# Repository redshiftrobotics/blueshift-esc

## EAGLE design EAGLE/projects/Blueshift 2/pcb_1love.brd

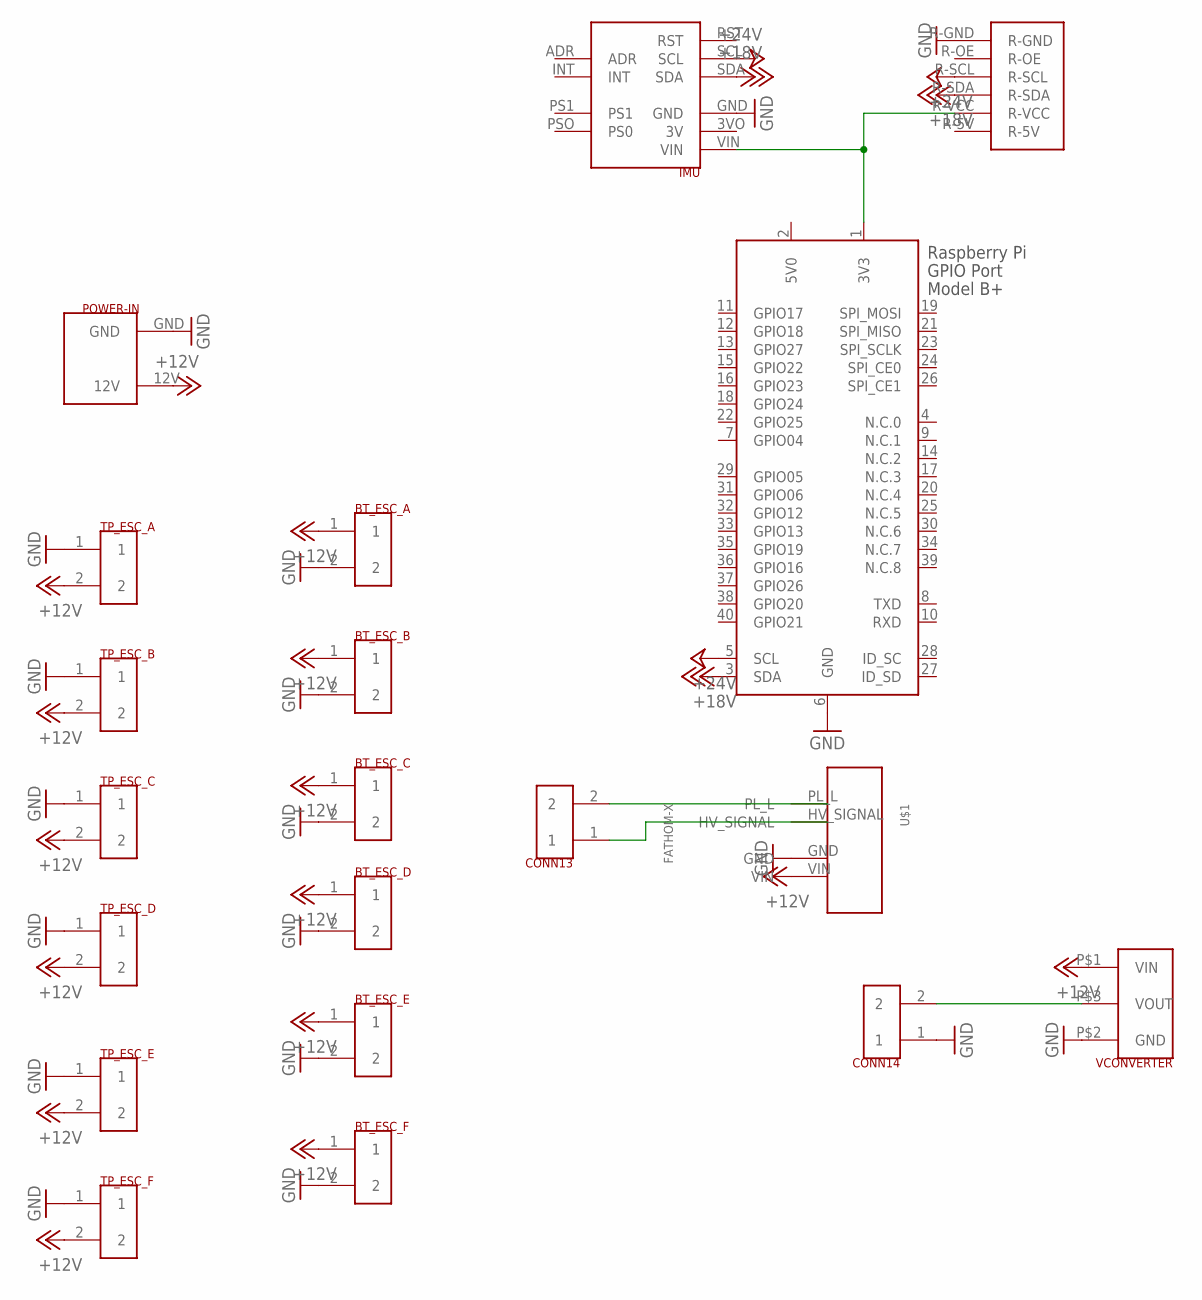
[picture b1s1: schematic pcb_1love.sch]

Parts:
BT_ESC_A: 2CONTACT_ULTRAFIT_R/A; 2CONTAC_ULTRAFIT_R/A
BT_ESC_B: 2CONTACT_ULTRAFIT_R/A; 2CONTAC_ULTRAFIT_R/A
BT_ESC_C: 2CONTACT_ULTRAFIT_R/A; 2CONTAC_ULTRAFIT_R/A
BT_ESC_D: 2CONTACT_ULTRAFIT_R/A; 2CONTAC_ULTRAFIT_R/A
BT_ESC_E: 2CONTACT_ULTRAFIT_R/A; 2CONTAC_ULTRAFIT_R/A
BT_ESC_F: 2CONTACT_ULTRAFIT_R/A; 2CONTAC_ULTRAFIT_R/A
CONN13, CONN14: 2CONTACT_ULTRAFIT_R/A; 2CONTAC_ULTRAFIT_R/A
IMU: IMU
POWER-IN: 2-CONTACT-SUPER
PWM_EXT: PWM_EXTENDER-SIMPLE
TP_ESC_A: 2CONTACT_ULTRAFIT_R/A; 2CONTAC_ULTRAFIT_R/A
TP_ESC_B: 2CONTACT_ULTRAFIT_R/A; 2CONTAC_ULTRAFIT_R/A
TP_ESC_C: 2CONTACT_ULTRAFIT_R/A; 2CONTAC_ULTRAFIT_R/A
TP_ESC_D: 2CONTACT_ULTRAFIT_R/A; 2CONTAC_ULTRAFIT_R/A
TP_ESC_E: 2CONTACT_ULTRAFIT_R/A; 2CONTAC_ULTRAFIT_R/A
TP_ESC_F: 2CONTACT_ULTRAFIT_R/A; 2CONTAC_ULTRAFIT_R/A
U$1: FATHOM-X
VCONVERTER: VOLTAGE_CONVERTER; VOLTAGE_CONVERTERS
X1: RASPI_BOARD_B+_F; RASPI_BOARD_B+_FULL

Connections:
5V0: X1.2 (5V0)
+12V: BT_ESC_A.1, BT_ESC_B.1, BT_ESC_C.1, BT_ESC_D.1, BT_ESC_E.1, BT_ESC_F.1, POWER-IN.12V, TP_ESC_A.2, TP_ESC_B.2, TP_ESC_C.2, TP_ESC_D.2, TP_ESC_E.2, TP_ESC_F.2, VCONVERTER.P$1 (VIN)
+18V: IMU.SDA, PWM_EXT.R-SDA, X1.3 (SDA)
+24V: IMU.SCL, PWM_EXT.R-SCL, X1.5 (SCL)
GND: BT_ESC_A.2, BT_ESC_B.2, BT_ESC_C.2, BT_ESC_D.2, BT_ESC_E.2, BT_ESC_F.2, CONN14.1, IMU.GND, POWER-IN.GND, PWM_EXT.R-GND, TP_ESC_A.1, TP_ESC_B.1, TP_ESC_C.1, TP_ESC_D.1, TP_ESC_E.1, TP_ESC_F.1, VCONVERTER.P$2 (GND), X1.6 (GND)
unnamed: CONN13.2, U$1.PL_L
unnamed: CONN13.1, U$1.HV_SIGNAL
unnamed: CONN14.2, VCONVERTER.P$3 (VOUT)
unnamed: IMU.VIN, PWM_EXT.R-VCC, X1.1 (3V3)

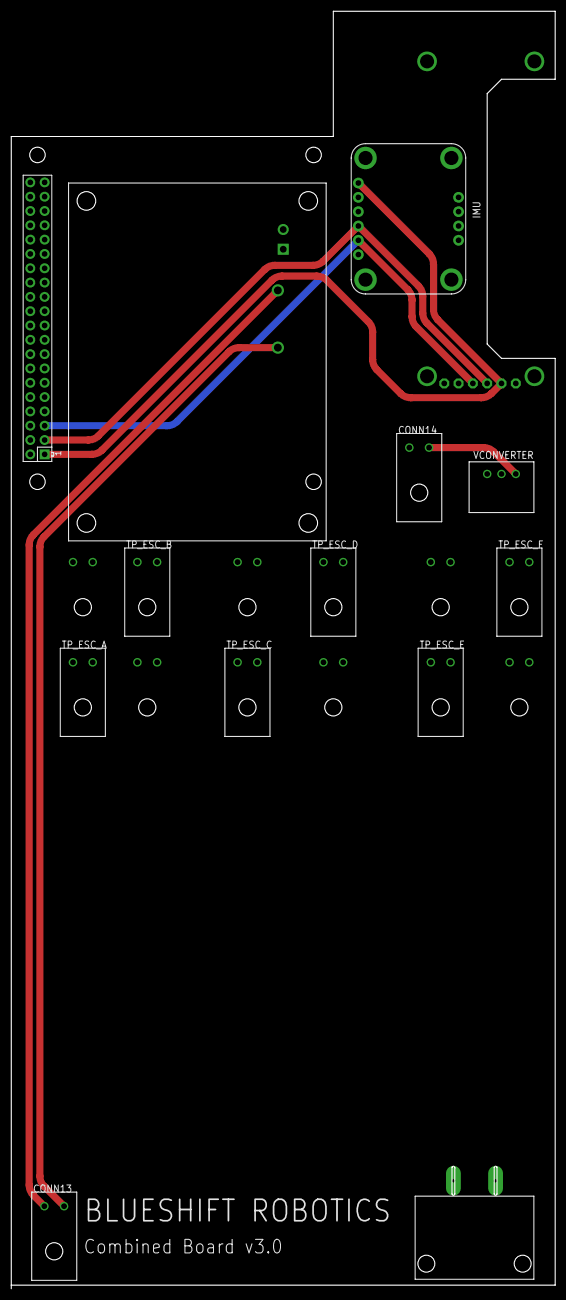
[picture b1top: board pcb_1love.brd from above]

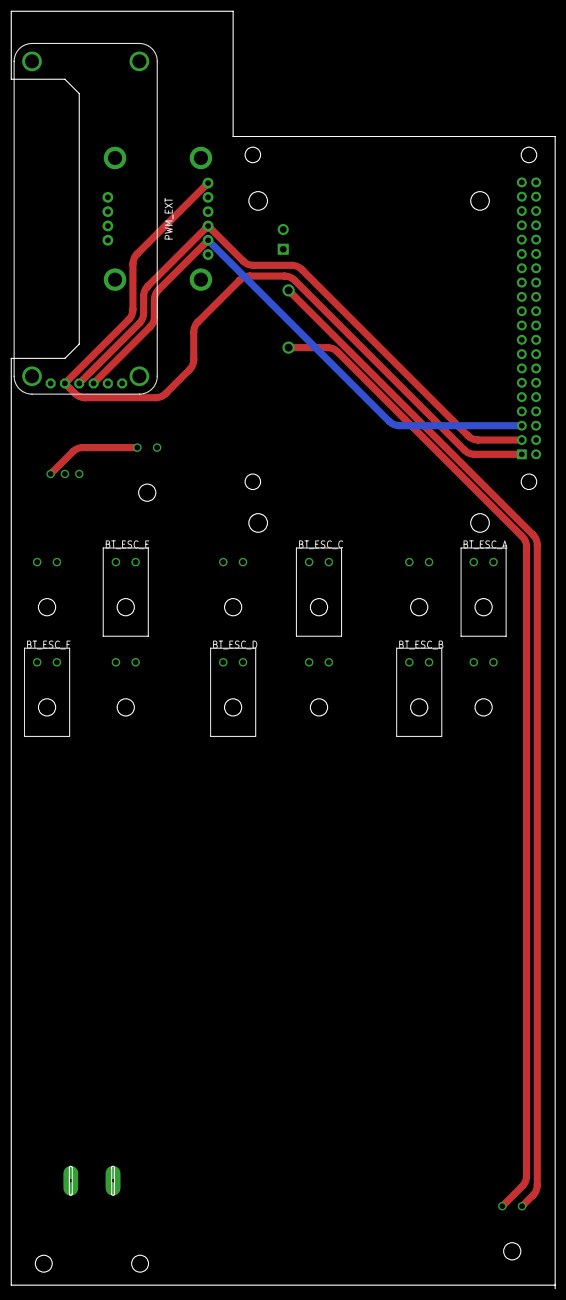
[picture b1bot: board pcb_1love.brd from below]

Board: 2 copper layers, 96.5 x 226.7 mm, 20 parts (7 on the bottom side), 8 nets.

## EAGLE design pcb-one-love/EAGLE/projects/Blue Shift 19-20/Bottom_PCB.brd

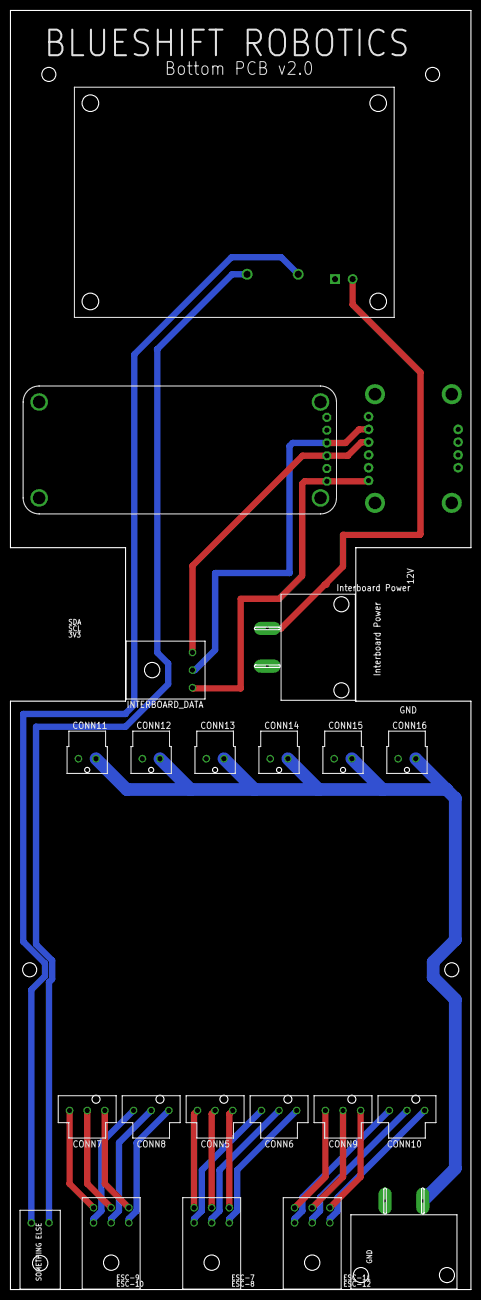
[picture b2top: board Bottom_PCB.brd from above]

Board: 2 copper layers, 91.4 x 254.0 mm, 22 parts (1 on the bottom side), 25 nets.

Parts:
CONN1: 2CONTAC_ULTRAFIT_R/A
CONN2, CONN3, CONN4: 6CONTACT_ULTRAFIT_R/A
CONN5, CONN6, CONN7, CONN8, CONN9, CONN10: 3CONTAC_ULTRAFIT_VERT
CONN11, CONN12, CONN13, CONN14, CONN15, CONN16: 2CONTAC_ULTRAFIT_VERT
IMU: IMU
INTERBOARD_DATA: 3CONTAC_ULTRAFIT_R/A
INTERBORD-POWER: 2-CONTACT-SUPER
POWER-IN: 2-CONTACT-SUPER
PWM1: PWM_EXTENDER-SIMPLE
U$1: FATHOM-X

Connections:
+3V3: IMU.VIN, INTERBOARD_DATA.3, PWM1.R-5V
+12V: CONN11.2, CONN12.2, CONN13.2, CONN14.2, CONN15.2, CONN16.2, INTERBORD-POWER.12V, POWER-IN.12V, U$1.VIN
GND: CONN11.1, CONN12.1, CONN13.1, CONN14.1, CONN15.1, CONN16.1, IMU.GND, INTERBORD-POWER.GND, POWER-IN.GND, PWM1.R-GND, U$1.GND
unnamed: CONN2.1-A, CONN5.3
unnamed: CONN2.1-B, CONN5.2
unnamed: CONN2.1-C, CONN5.1
unnamed: CONN2.2-A, CONN6.3
unnamed: CONN2.2-B, CONN6.2
unnamed: CONN2.2-C, CONN6.1
unnamed: CONN3.1-A, CONN7.3
unnamed: CONN3.1-B, CONN7.2
unnamed: CONN3.1-C, CONN7.1
unnamed: CONN3.2-A, CONN8.3
unnamed: CONN3.2-B, CONN8.2
unnamed: CONN3.2-C, CONN8.1
unnamed: CONN1.2, U$1.PL_L
unnamed: CONN1.1, U$1.HV_SIGNAL
unnamed: CONN4.1-A, CONN9.3
unnamed: CONN4.1-B, CONN9.2
unnamed: CONN4.1-C, CONN9.1
unnamed: CONN4.2-A, CONN10.3
unnamed: CONN4.2-B, CONN10.2
unnamed: CONN4.2-C, CONN10.1
unnamed: IMU.SCL, INTERBOARD_DATA.2, PWM1.R-SCL
unnamed: IMU.SDA, INTERBOARD_DATA.1, PWM1.R-SDA

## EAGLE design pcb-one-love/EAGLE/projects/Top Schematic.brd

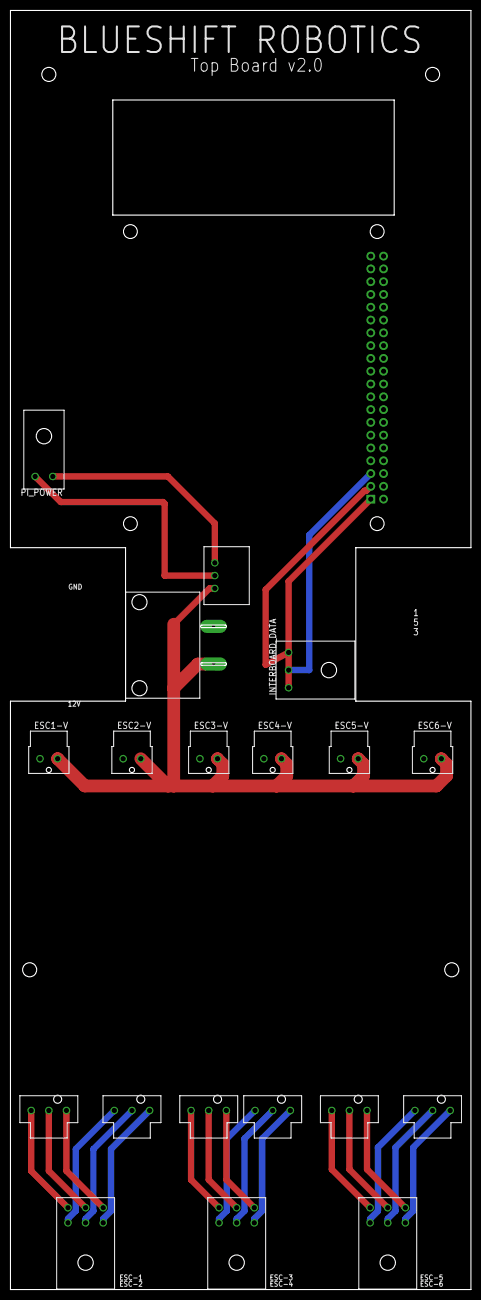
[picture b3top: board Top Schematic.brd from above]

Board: 2 copper layers, 91.4 x 254.0 mm, 20 parts (1 on the bottom side), 24 nets.

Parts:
CONN1, CONN2, CONN3: 6CONTACT_ULTRAFIT_R/A
ESC1-M, ESC2-M, ESC3-M, ESC4-M, ESC5-M, ESC6-M: 3CONTAC_ULTRAFIT_VERT
ESC1-V, ESC2-V, ESC3-V, ESC4-V, ESC5-V, ESC6-V: 2CONTAC_ULTRAFIT_VERT
INTERBOARD-POWER: 2-CONTACT-SUPER
INTERBOARD_DATA: 3CONTAC_ULTRAFIT_R/A
PI_POWER: 2CONTAC_ULTRAFIT_R/A
VOLTAGE_CONVERTER: VOLTAGE_CONVERTERS
X1: RASPI_BOARD_B+_F; RASPI_BOARD_B+_FULL

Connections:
+3V3: INTERBOARD_DATA.1, X1.1
+12V: ESC1-V.2, ESC2-V.2, ESC3-V.2, ESC4-V.2, ESC5-V.2, ESC6-V.2, INTERBOARD-POWER.12V, VOLTAGE_CONVERTER.P$2
GND: ESC1-V.1, ESC2-V.1, ESC3-V.1, ESC4-V.1, ESC5-V.1, ESC6-V.1, INTERBOARD-POWER.GND, PI_POWER.2, VOLTAGE_CONVERTER.P$1, X1.6
unnamed: CONN3.1-A, ESC5-M.3
unnamed: CONN3.1-B, ESC5-M.2
unnamed: CONN3.1-C, ESC5-M.1
unnamed: CONN3.2-A, ESC6-M.3
unnamed: CONN3.2-B, ESC6-M.2
unnamed: CONN3.2-C, ESC6-M.1
unnamed: CONN2.2-C, ESC4-M.1
unnamed: CONN1.1-B, ESC1-M.2
unnamed: CONN2.2-B, ESC4-M.2
unnamed: CONN2.2-A, ESC4-M.3
unnamed: CONN1.2-B, ESC2-M.2
unnamed: CONN2.1-C, ESC3-M.1
unnamed: INTERBOARD_DATA.2, X1.5
unnamed: INTERBOARD_DATA.3, X1.3
unnamed: PI_POWER.1, VOLTAGE_CONVERTER.P$3
unnamed: CONN2.1-A, ESC3-M.3
unnamed: CONN2.1-B, ESC3-M.2
unnamed: CONN1.2-C, ESC2-M.1
unnamed: CONN1.2-A, ESC2-M.3
unnamed: CONN1.1-C, ESC1-M.1
unnamed: CONN1.1-A, ESC1-M.3

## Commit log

2020-03-08 Initial Comet
2020-03-26 moose
2020-04-30 Fix power to IMU and PWM, RasPi cutout
2020-05-04 Re-position components
2020-05-05 Add wires and cutout for new layout
2020-05-05 change corners
2020-05-05 Link eagle and fusion
2020-05-08 fix github
2020-05-08 fix .sch
2020-05-08 fixed hole in pcb
2020-05-08 Update RasPi IO Hole
2020-05-19 Fix issue where power and ground aren't connected the Fathom X
2020-08-29 PCB One Love complete
2020-08-29 Remove .DS_Store
2020-11-25 added math for clarke-park transform and motortest
2020-11-25 Update motortest
2020-11-27 Fix bugs in motortest.ino
2020-11-27 Finish motor_test logging and make naming scheme consistent
2020-11-27 Fix bugs in motor_test_logging
2020-11-27 Clean up documentation
2020-12-09 Add MCU part
2020-12-09 Added 10uf capacitor
2020-12-17 Add 3 phase inverter, Jonathon ESC
2020-12-19 Added current sensors, updated port direction, changed VCC to 3V3
2020-12-19 Renamed ports, remapped programming pins, added voltage dividers
2020-12-20 Added footprint of capacitor
2020-12-20 Added footprints, resolved errors
2021-01-22 Changed direction of power connected mosfets
2021-01-22 Add Active BOM
2021-01-28 Update ActiveBOM
2021-02-27 Add 220 Ohm resistor to Three Phase Inverter, connect decoupling capacitors to ground plane
2021-03-03 Add shunt resistor footprint and model
2021-03-03 Remove data and power pads from BOM
2021-03-05 Change voltage divider to output 5V max
2021-03-06 Poorly began 3 phase inverter on board layout
2021-03-06 created rough layout of board
2021-03-06 Replace MOSFETS from Altium Content Vault with custom schematic/footprint because the 3d model was in the wrong place
2021-03-06 Add fixed MOSFET 3d model
2021-03-06 Update MOSFET model again because the last one was backwards and inside the PCB
2021-03-07 Finish top layer layout
2021-03-08 Update Top Layer, distinguish ground and 3V3 layer
2021-03-08 Add current limiting resistors and MCLR circuit on the bottom layer, and current measuring circuit on the top layer
2021-03-08 Continue bottom layer layout
2021-03-08 Fix MOSFETs inside PCB
2021-03-13 calm before the chaos and immenent destruction of the work so far
2021-03-18 routed all wires except for programming pins on bottom layer, set i2c pins as pads
2021-03-18 All wires are routed! V1 is done. (DRC violations are not yet fixed)
2021-03-19 Add PIC LED test environment
2021-03-20 Basic LED blinking code
2021-03-20 Update .gitignore to remove MPLAB X IDE build data
2021-03-20 feat: turn led on with button press
2021-03-20 add 6 mm to width, change MCU to SOIC, eliminate ALL DRC violations :)
2021-03-23 Get timer/interrupt led blinking working
2021-03-24 In progress PWM generation
2021-03-24 Center Aligned PWM is working!!
2021-03-24 Add LED dimming code
2021-03-26 Fix bug in duty cycle updating and delay
2021-03-26 in progress: setup ADC
2021-03-26 in progress: trigger ADC with PWM and interrupt generation
2021-03-26 changed voltage divider, moved mounting holes, ckeaned up and solved the board, cleared design rule check again
2021-03-27 Update adc sampling code (still not working)
2021-03-27 analog sampling working!
2021-03-27 Crude led dimming based on adc input
2021-03-27 Add trapezoidal control starting files
2021-03-28 Start trapezoidal control code
2021-03-28 First iteration of open-loop trapezoidal control code (not tested)
2021-03-30 wire clean up
2021-04-01 broken and dead
2021-04-01 change high n-channel to p-channel MOSFETs, changed i2c pins to give analog wire space
2021-04-02 Clean up some wires
2021-04-03 Update design rules to fit JLC, solved board's violations
2021-04-03 Added label on silkscreen
2021-04-03 add TX and RX through hole pads
2021-04-03 remove mounting hole label, move silkscreen labels for RX and TX
2021-04-06 change voltage divider to 0603 resistors
2021-04-06 Clean up some last few wires
2021-04-06 Fix DRC Violations
2021-04-06 mounting holes moved, board tidied up, drc cleared
2021-04-06 extra wire cleanup
2021-04-06 add gerber file, nc drill, clean wires
2021-04-06 Update BOM for final ordering V1
2021-04-06 Add NC Drill files to outjob
2021-04-06 Update outjob
2021-04-06 fix up wiring, final version 1.0
2021-04-06 Update output job files
2021-04-06 Add gerber outline
2021-04-11 Add color to pdf outputs of outjob file
2021-04-11 Save PrjPcb
2021-04-11 Update PrjPcb release settings to use new outjob files
2021-04-12 Work on Clarke, Park, and PID
2021-04-12 Working Clarke and Park
2021-04-23 Finish PID
2021-04-27 add pull down resistors and BJT transistor circuit to Three Phase Inverter
2021-04-28 Layout p-channel gate driver and n channel gate pull down on pcb
2021-04-29 switch 10k and 100k resistors for high side MOSFETS, clear drc
2021-04-30 switch p channel mosfet on state
2021-04-30 begin updating MOSFET connection type, update MOSFET footprint
2021-05-03 make progress on DRC, change via size to 1.3, DRC not cleared
2021-05-03 Add new npn transistor to library
2021-05-04 clear DRC, clean up wires
2021-05-04 Clean up general PCB routing
2021-05-04 Resolve DRC violations
2021-05-04 finish version 1.1!!! clean up wires, change fet connection types again.
2021-05-04 finalize wire cleanup and connectivity
2021-05-04 change fab output settings, Jonathan v1.1 release!
2021-05-05 Update Alpha-Beta Filter
2021-05-20 Organize arduino testing code
2021-05-20 Reconfigure code directory structure
2021-05-20 Add neccessary mplab project configuration files
2021-05-20 Add I2C testing code
2021-05-21 working motor driving code
2021-05-22 change vref of current sensor to 3V3. reroute and clear drc with schematic changes
2021-05-23 Partially working I2C
    the pic can be detected, but read/write logic is not yet implemented
2021-05-23 Upload ex. code for i2c follower and leader
2021-05-25 [not-working] in progress i2c testing tcode
2021-05-25 Fix I2C!!
2021-05-25 Increase timer speed
2021-05-25 [in-progress] add i2c communication to trapezoidal control
2021-05-25 Correctly add i2c files to mplab project to fix compile errors
2021-05-29 Update frequency to 20kHz
2021-05-29 [in progress] implement closed loop trapezoidal control
2021-05-30 [in progress] functional open loop motor control
2021-05-30 [in progress] add zero crossing detection with half the dc bus voltage
2021-05-30 [in progress] test zero crossing detection outputting commutation events on tx
2021-06-22 Clean up code, debugging why pwm is not triggering adc
2021-06-23 Change timer 1 to timer 2
2021-06-23 Fix bugs in led_test and update commutation code in trapezoidal_control
2021-06-23 Add timer 2
2021-06-23 fix timer 2 commutation interrupt buv
2021-06-24 Add adc folder and convert adc units
2021-06-24 simplify adc triggers
2021-06-24 Update mplab project with adc files
2021-06-24 bitbang pwm to access adc values
2021-06-24 fixed math
2021-06-24 Update voltage divider for both R1 and R2 of the voltage divider for the high side MOSFETs
2021-06-25 back emf detetection working for phase a
2021-06-25 functional trapezoidal control
2021-06-25 acutally functional trapezoidal control (removed unnecessary 1ms delay)
2021-08-08 Made led_test functional (sort of)
2021-08-09 Changed 1 to 2
2022-01-15 fix i2c clock stretching
2022-05-03 Added LED
    Blue LED and resistor connected to MCU pin 14.
2022-05-03 Changed Screw Size
    M2 -> M2.5
2022-05-30 Redo PCB layout to clean up everything
    Still need to fix some DRC violations
2022-06-10 Fix Kavi's bad code
2022-06-24 Clean up analog routing
2022-06-24 Simplify MCLR Circuit
2022-06-24 Clean up routing
    3V3 and UART
2022-06-25 Finish 2.0 layout except for DRC Violations
2022-06-25 Fix all DRC Violations (v2.0 done)
2022-06-27 Fix all DRC violations (altium please don't delete my work)
2022-06-28 kavi is the best at code
2022-06-29 Tune open loop trapezoidal control
2022-06-29 Add serial test code
2022-06-29 Clean up oscillator code
2022-06-29 Working multi-line multi-character serial
2022-06-29 Increase baud rate
2022-06-30 Switch to normal interrupt syntax
2022-06-30 Replace printf with custom print function to save space
2022-06-30 add float to char and serial to trapezoidal
2022-06-30 Fix issue in float_to_char usage
2022-06-30 Add serial to trapezoidal control
2022-06-30 Fix ADC math and clean up code
2022-07-03 Clean up PCB
    align mosfets
    increase trace thickness
    generally clean up routing and silkscreen
2022-07-04 Clean up analog section
    Flip connection to differential amplifier
    increase trace thickness
    disconnect the no connect pin on the differential amplifier
2022-07-05 kind of working lmao
2022-07-05 actually working this time
2022-07-05 All three phase voltage measurements working
2022-07-05 fix comment
2022-07-09 Update trapezoidal control code
2022-07-10 Convert all MCU pins to multiselect
2022-07-14 Almost working trapezoidal control
2022-07-18 Clean up DRC Violations + increase 3V3 via size
2022-07-18 Play sounds (Disables commutation)
2022-07-18 Increase size of BJT transistor pads
2022-07-18 Properly label PGEC/PGED in addition to SDA/SCL
2022-07-18 Clean up code (untested) and update pcb config
2022-07-18 Add timer math explanation
2022-07-19 Separate PWM code into its own file
2022-07-19 Add set_duty_cycle function for easy adc trigger point adjustment
2022-07-20 Fix typo in motor state commutation functions
2022-07-20 the little esc
    Play first 4 bars of under the sea on loop
2022-07-21 In progress state machine
2022-07-21 Closed loop works
2022-07-25 Switch to QFN-S version of pic
    new layout done, silkscreen in place but need to fix drc violations
2022-07-29 Fix all drc violations
    moved around some components and parts of silkscreen. Its pretty cramped which will make reading it for manufacturing hard, but I don't think there is a better way.
2022-07-29 Clean up code
2022-08-10 Enable language counter for EDA files
    https://github.com/redshiftrobotics/blueshift-motherboard/pull/2
2022-08-11 Fixed i2c
    AAAAAAAAAAHHHHHHHHHHHHHHHHHHHHHHHHHHHHHHHHHHHHHHHHHHHHHHHHHHHHHHHHHHHHHHHHHHHHHHHHHHHHHHHHHHHHHHHHHHHHHHHHHHHHHHHHHHHHHHHHHHHHHHHH
2022-08-11 Uncomment i2c in main.c
2022-08-11 Make i2c work
    The big changes here is the new header file with registers for i2c, the next big change is the read and write registers functons in i2c.c which are used for the functions that are called when writing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
2022-08-11 Remove uneccesarry library
2022-08-12 Make invalidCommand work
    We made it so that when reading/writing i2c the register ivalid command works
2022-08-13 Reset Code :0
    I got the i2c code to reset when writing to reg 3 and lastcommandsuccess and lastcommandinvalid should also work
2022-08-13 Add reset Register
2022-08-19 Horrible not working i2c code
    Doesnt work dont try
2022-08-20 Add comments to distinguish words from regular registers
